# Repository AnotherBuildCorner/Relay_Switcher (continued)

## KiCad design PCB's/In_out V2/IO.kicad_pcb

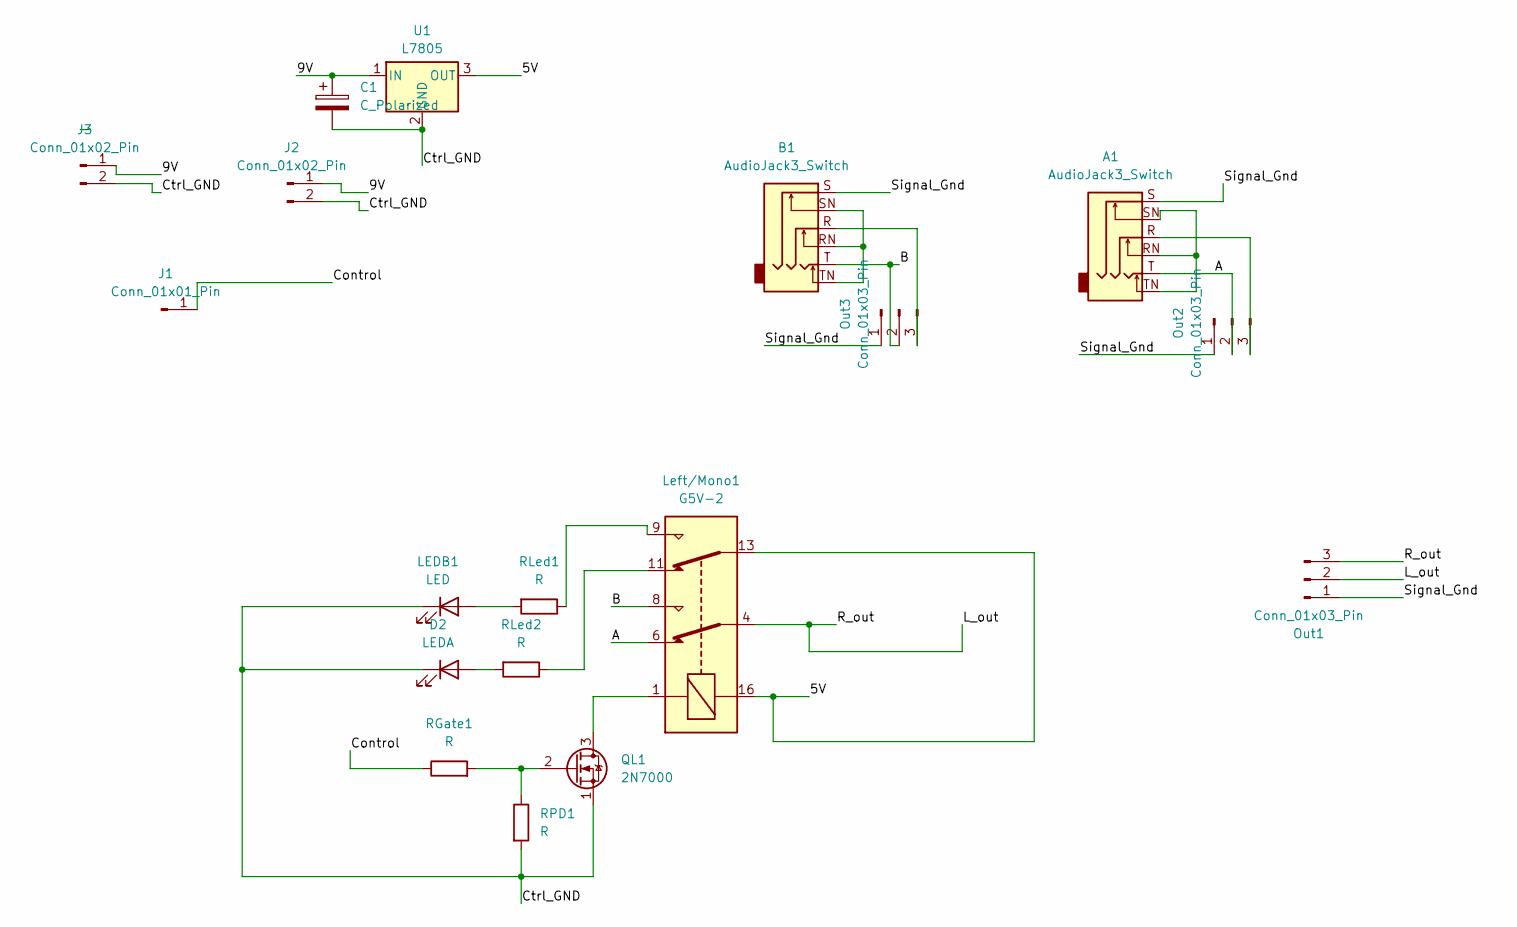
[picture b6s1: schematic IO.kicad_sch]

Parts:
A1: AudioJack3_Switch; Jack_6.35mm_Neutrik_NMJ6HFD3_Horizontal
B1: AudioJack3_Switch; Jack_6.35mm_Neutrik_NMJ6HFD3_Horizontal
C1: C_Polarized; CP_Radial_D10.0mm_P3.50mm
D2: LEDA; LED_D5.0mm
J1: Conn_01x01_Pin; PinHeader_1x01_P2.54mm_Vertical
J2, J3: Conn_01x02_Pin; PinHeader_2x01_P2.54mm_Vertical
LEDB1: LED; LED_D5.0mm
Left/Mono1: G5V-2; Relay_DPDT_Omron_G5V-2
Out1, Out2, Out3: Conn_01x03_Pin; PinHeader_1x03_P2.54mm_Vertical
QL1: 2N7000; TO-92_Inline
RGate1: R; R_Axial_DIN0207_L6.3mm_D2.5mm_P7.62mm_Horizontal
RLed1, RLed2: R; R_Axial_DIN0207_L6.3mm_D2.5mm_P7.62mm_Horizontal
RPD1: R; R_Axial_DIN0207_L6.3mm_D2.5mm_P7.62mm_Horizontal
U1: L7805; TO-220-3_Vertical

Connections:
/5V: Left/Mono1.13, Left/Mono1.16, U1.3 (OUT)
/9V: C1.1, J2.1, J3.1, U1.1 (IN)
/A: A1.T, Left/Mono1.6, Out2.2
/B: B1.T, Left/Mono1.8, Out3.2
/Control: J1.1, RGate1.1
/Ctrl_GND: C1.2, D2.1 (K), J2.2, J3.2, LEDB1.1 (K), QL1.1 (S), RPD1.2, U1.2 (GND)
/L_out: Left/Mono1.4, Out1.2, Out1.3
/Signal_Gnd: A1.S, B1.S, Out1.1, Out2.1, Out3.1
unnamed: A1.RN, A1.SN, A1.TN
unnamed: B1.RN, B1.SN, B1.TN
unnamed: D2.2 (A), RLed2.2
unnamed: LEDB1.2 (A), RLed1.2
unnamed: Left/Mono1.9, RLed1.1
unnamed: Left/Mono1.11, RLed2.1
unnamed: A1.R, Out2.3
unnamed: B1.R, Out3.3
unnamed: Left/Mono1.1, QL1.3 (D)
unnamed: QL1.2 (G), RGate1.2, RPD1.1

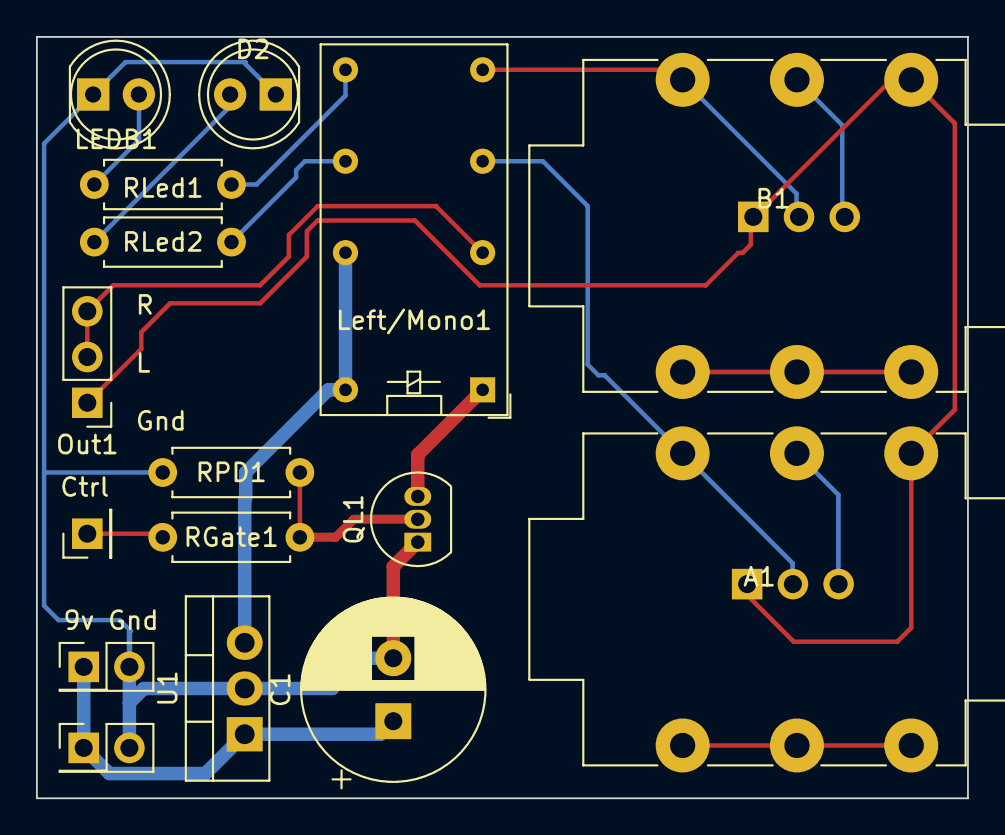
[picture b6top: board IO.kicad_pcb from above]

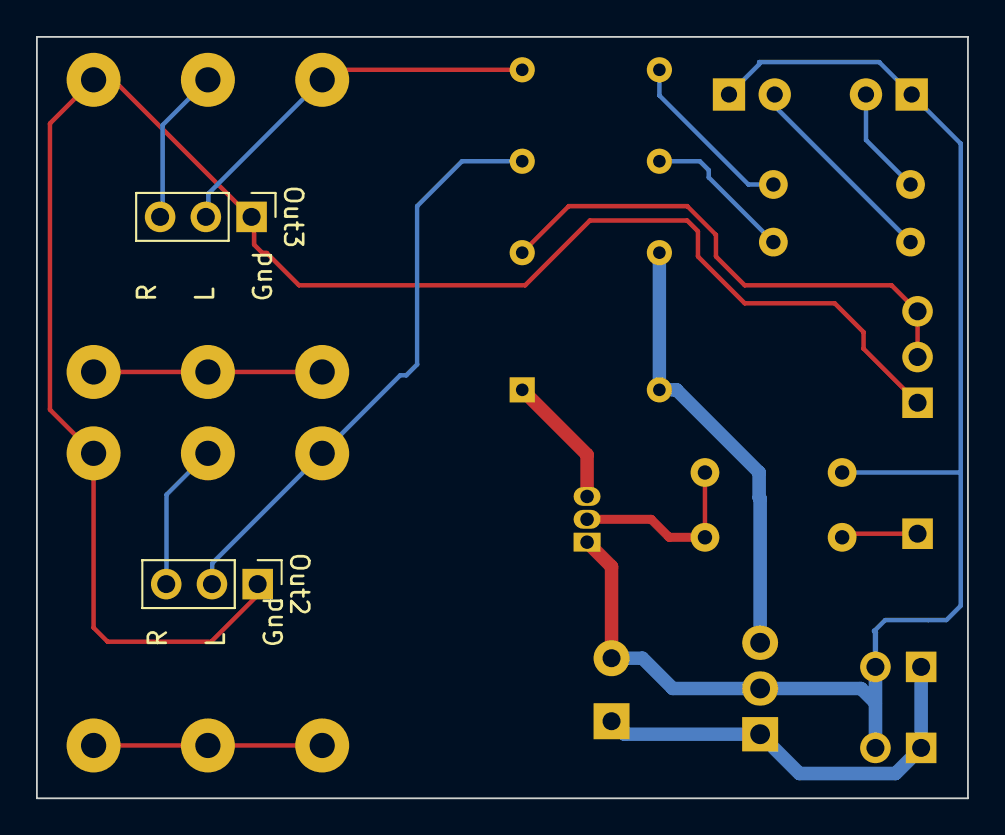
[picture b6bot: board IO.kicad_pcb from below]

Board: 2 copper layers, 51.7 x 42.3 mm, 18 parts (2 on the bottom side), 18 nets.

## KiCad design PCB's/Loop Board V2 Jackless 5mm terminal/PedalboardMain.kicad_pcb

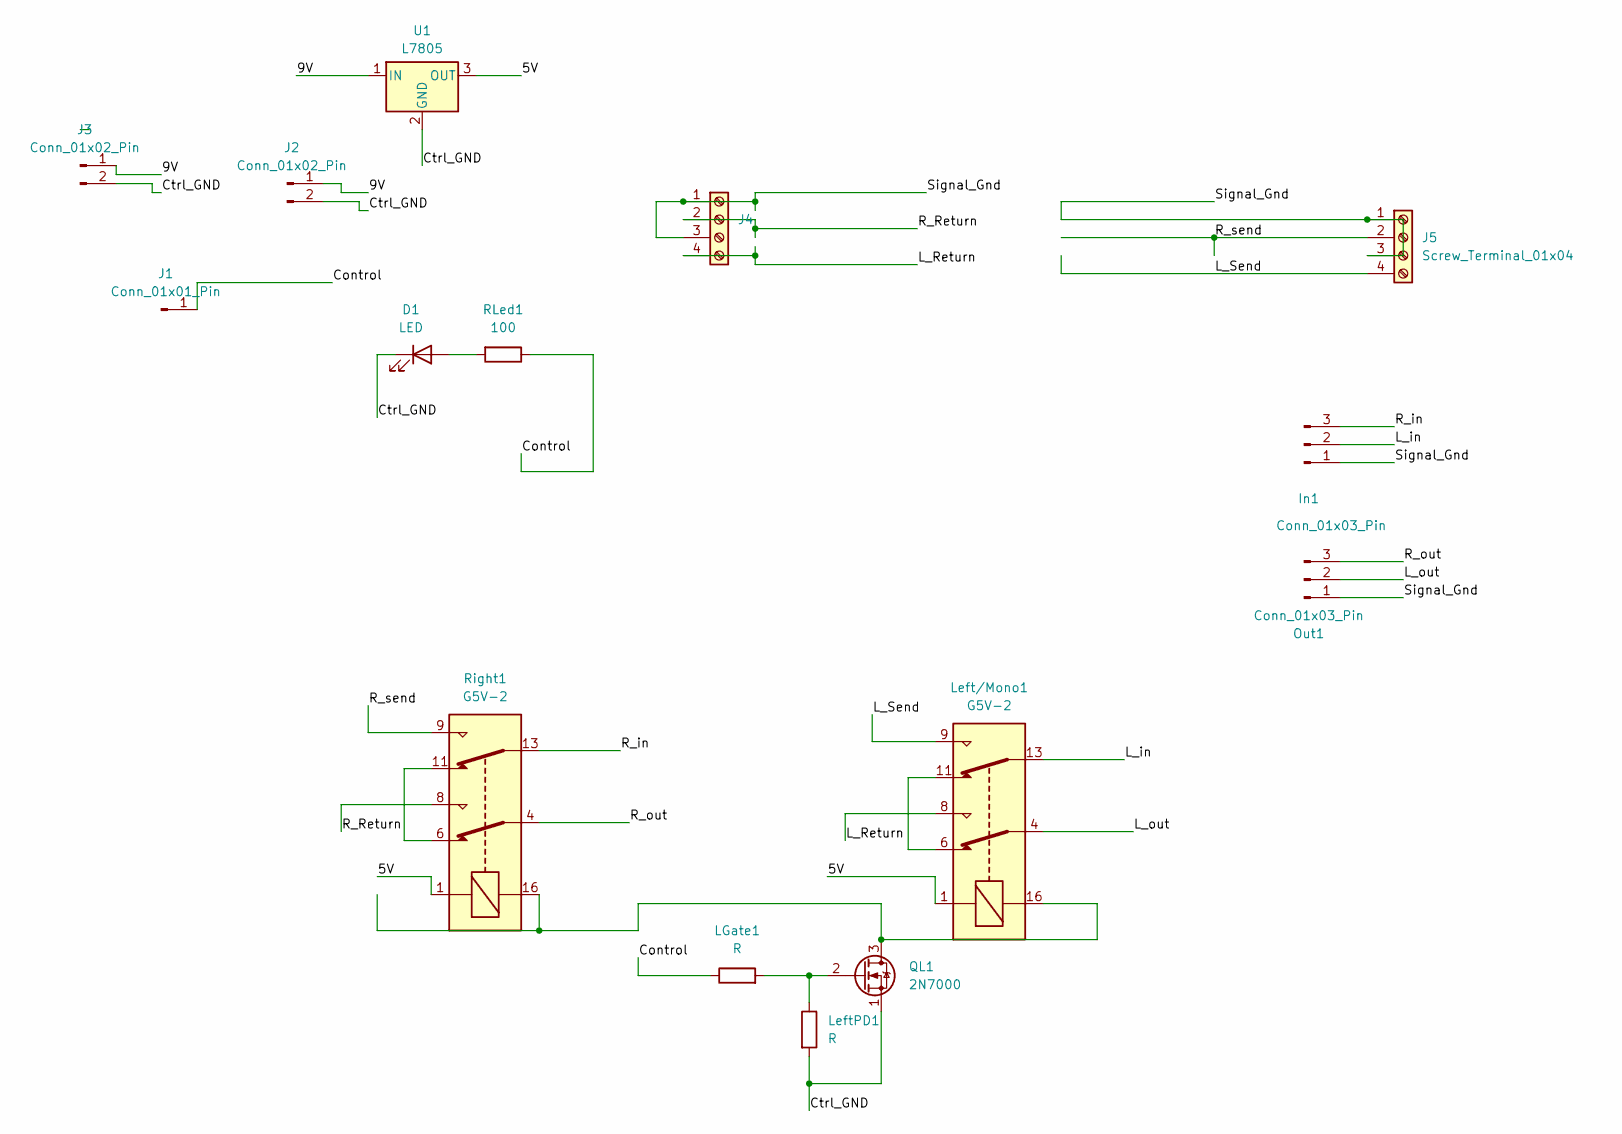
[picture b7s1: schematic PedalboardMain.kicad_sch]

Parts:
D1: LED; LED_D5.0mm
In1: Conn_01x03_Pin; PinHeader_1x03_P2.54mm_Vertical
J1: Conn_01x01_Pin; PinHeader_1x01_P2.54mm_Vertical
J2, J3: Conn_01x02_Pin; PinHeader_2x01_P2.54mm_Vertical
J4, J5: Screw_Terminal_01x04; CUI_TB001-500-04BE
LGate1: R; R_Axial_DIN0207_L6.3mm_D2.5mm_P7.62mm_Horizontal
Left/Mono1: G5V-2; Relay_DPDT_Omron_G5V-2
LeftPD1: R; R_Axial_DIN0207_L6.3mm_D2.5mm_P7.62mm_Horizontal
Out1: Conn_01x03_Pin; PinHeader_1x03_P2.54mm_Vertical
QL1: 2N7000; TO-92_Inline
RLed1: 100; R_Axial_DIN0207_L6.3mm_D2.5mm_P7.62mm_Horizontal
Right1: G5V-2; Relay_DPDT_Omron_G5V-2
U1: L7805; TO-220-3_Vertical

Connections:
/5V: Left/Mono1.1, Right1.1, U1.3 (OUT)
/9V: J2.1, J3.1, U1.1 (IN)
/Control: J1.1, LGate1.1, RLed1.1
/Ctrl_GND: D1.1 (K), J2.2, J3.2, LeftPD1.2, QL1.1 (S), U1.2 (GND)
/L_Return: J4.4, Left/Mono1.8
/L_Send: J5.4, Left/Mono1.9
/L_in: In1.2, Left/Mono1.13
/L_out: Left/Mono1.4, Out1.2
/R_Return: J4.2, Right1.8
/R_in: In1.3, Right1.13
/R_out: Out1.3, Right1.4
/R_send: J5.2, Right1.9
/Signal_Gnd: In1.1, J4.1, J4.3, J5.1, J5.3, Out1.1
unnamed: D1.2 (A), RLed1.2
unnamed: Left/Mono1.6, Left/Mono1.11
unnamed: Left/Mono1.16, QL1.3 (D), Right1.16
unnamed: LGate1.2, LeftPD1.1, QL1.2 (G)
unnamed: Right1.6, Right1.11

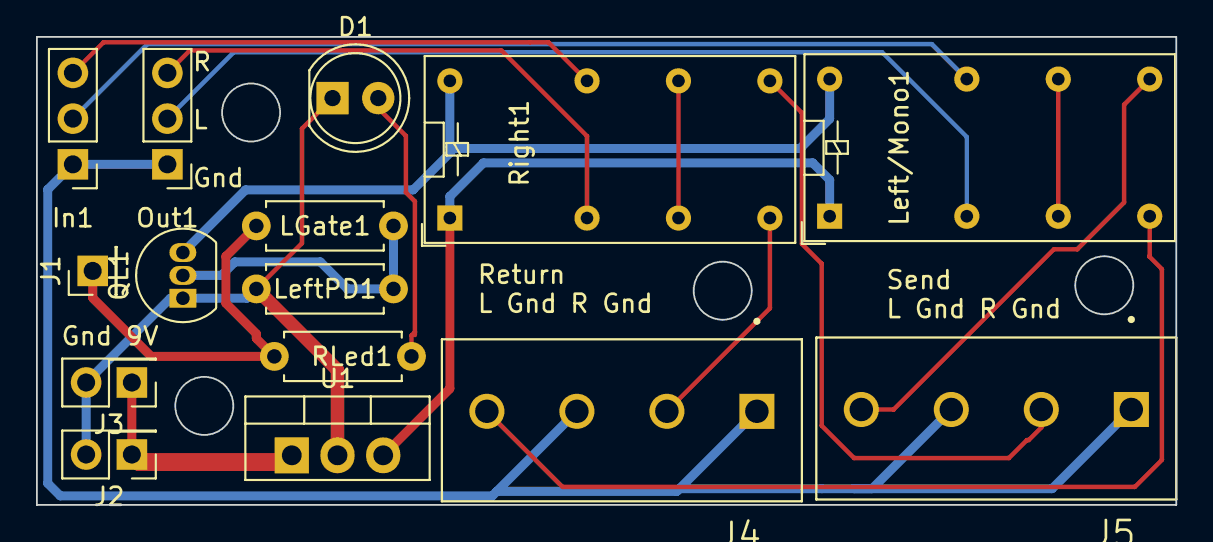
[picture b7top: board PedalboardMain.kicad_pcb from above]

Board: 2 copper layers, 63.3 x 26.0 mm, 15 parts (0 on the bottom side), 18 nets.

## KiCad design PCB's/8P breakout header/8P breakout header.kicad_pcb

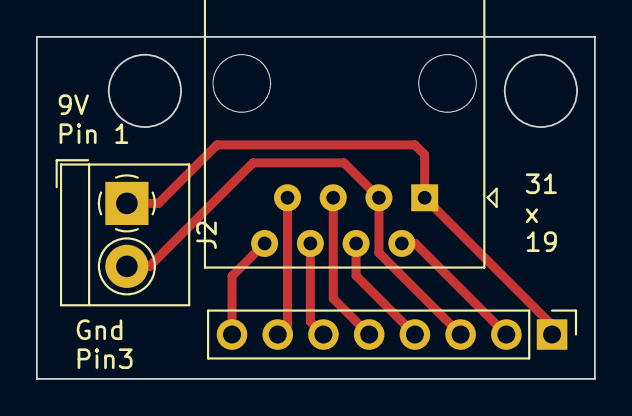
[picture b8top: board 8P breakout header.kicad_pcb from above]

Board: 2 copper layers, 31.0 x 19.0 mm, 3 parts (0 on the bottom side), 8 nets.

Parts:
J1: 8P8C; RJ45_Amphenol_54602-x08_Horizontal
J2: Screw_Terminal_01x02; TerminalBlock_4Ucon_1x02_P3.50mm_Horizontal
J4: Conn_01x08_Pin; PinHeader_1x08_P2.54mm_Vertical

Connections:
unnamed: J1.1, J2.1, J4.1
unnamed: J1.3, J2.2, J4.3
unnamed: J1.2, J4.2
unnamed: J1.4, J4.4
unnamed: J1.5, J4.5
unnamed: J1.6, J4.6
unnamed: J1.7, J4.7
unnamed: J1.8, J4.8

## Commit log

2024-06-08 new PCBs
2024-06-10 Pcb load
2024-07-15 latest Version PCBs
2024-07-15 added 3d models
2024-07-16 code load
2024-08-12 fully working v1
2024-11-02 push
2025-02-09 Added V3
2025-02-09 edit README
2025-02-09 V3 Added Complete
2025-02-09 photo correction
2025-02-09 updated notes
2025-02-09 last update
